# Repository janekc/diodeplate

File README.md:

# diodeplate
Plateshaped example PCB design for a portable partylamp

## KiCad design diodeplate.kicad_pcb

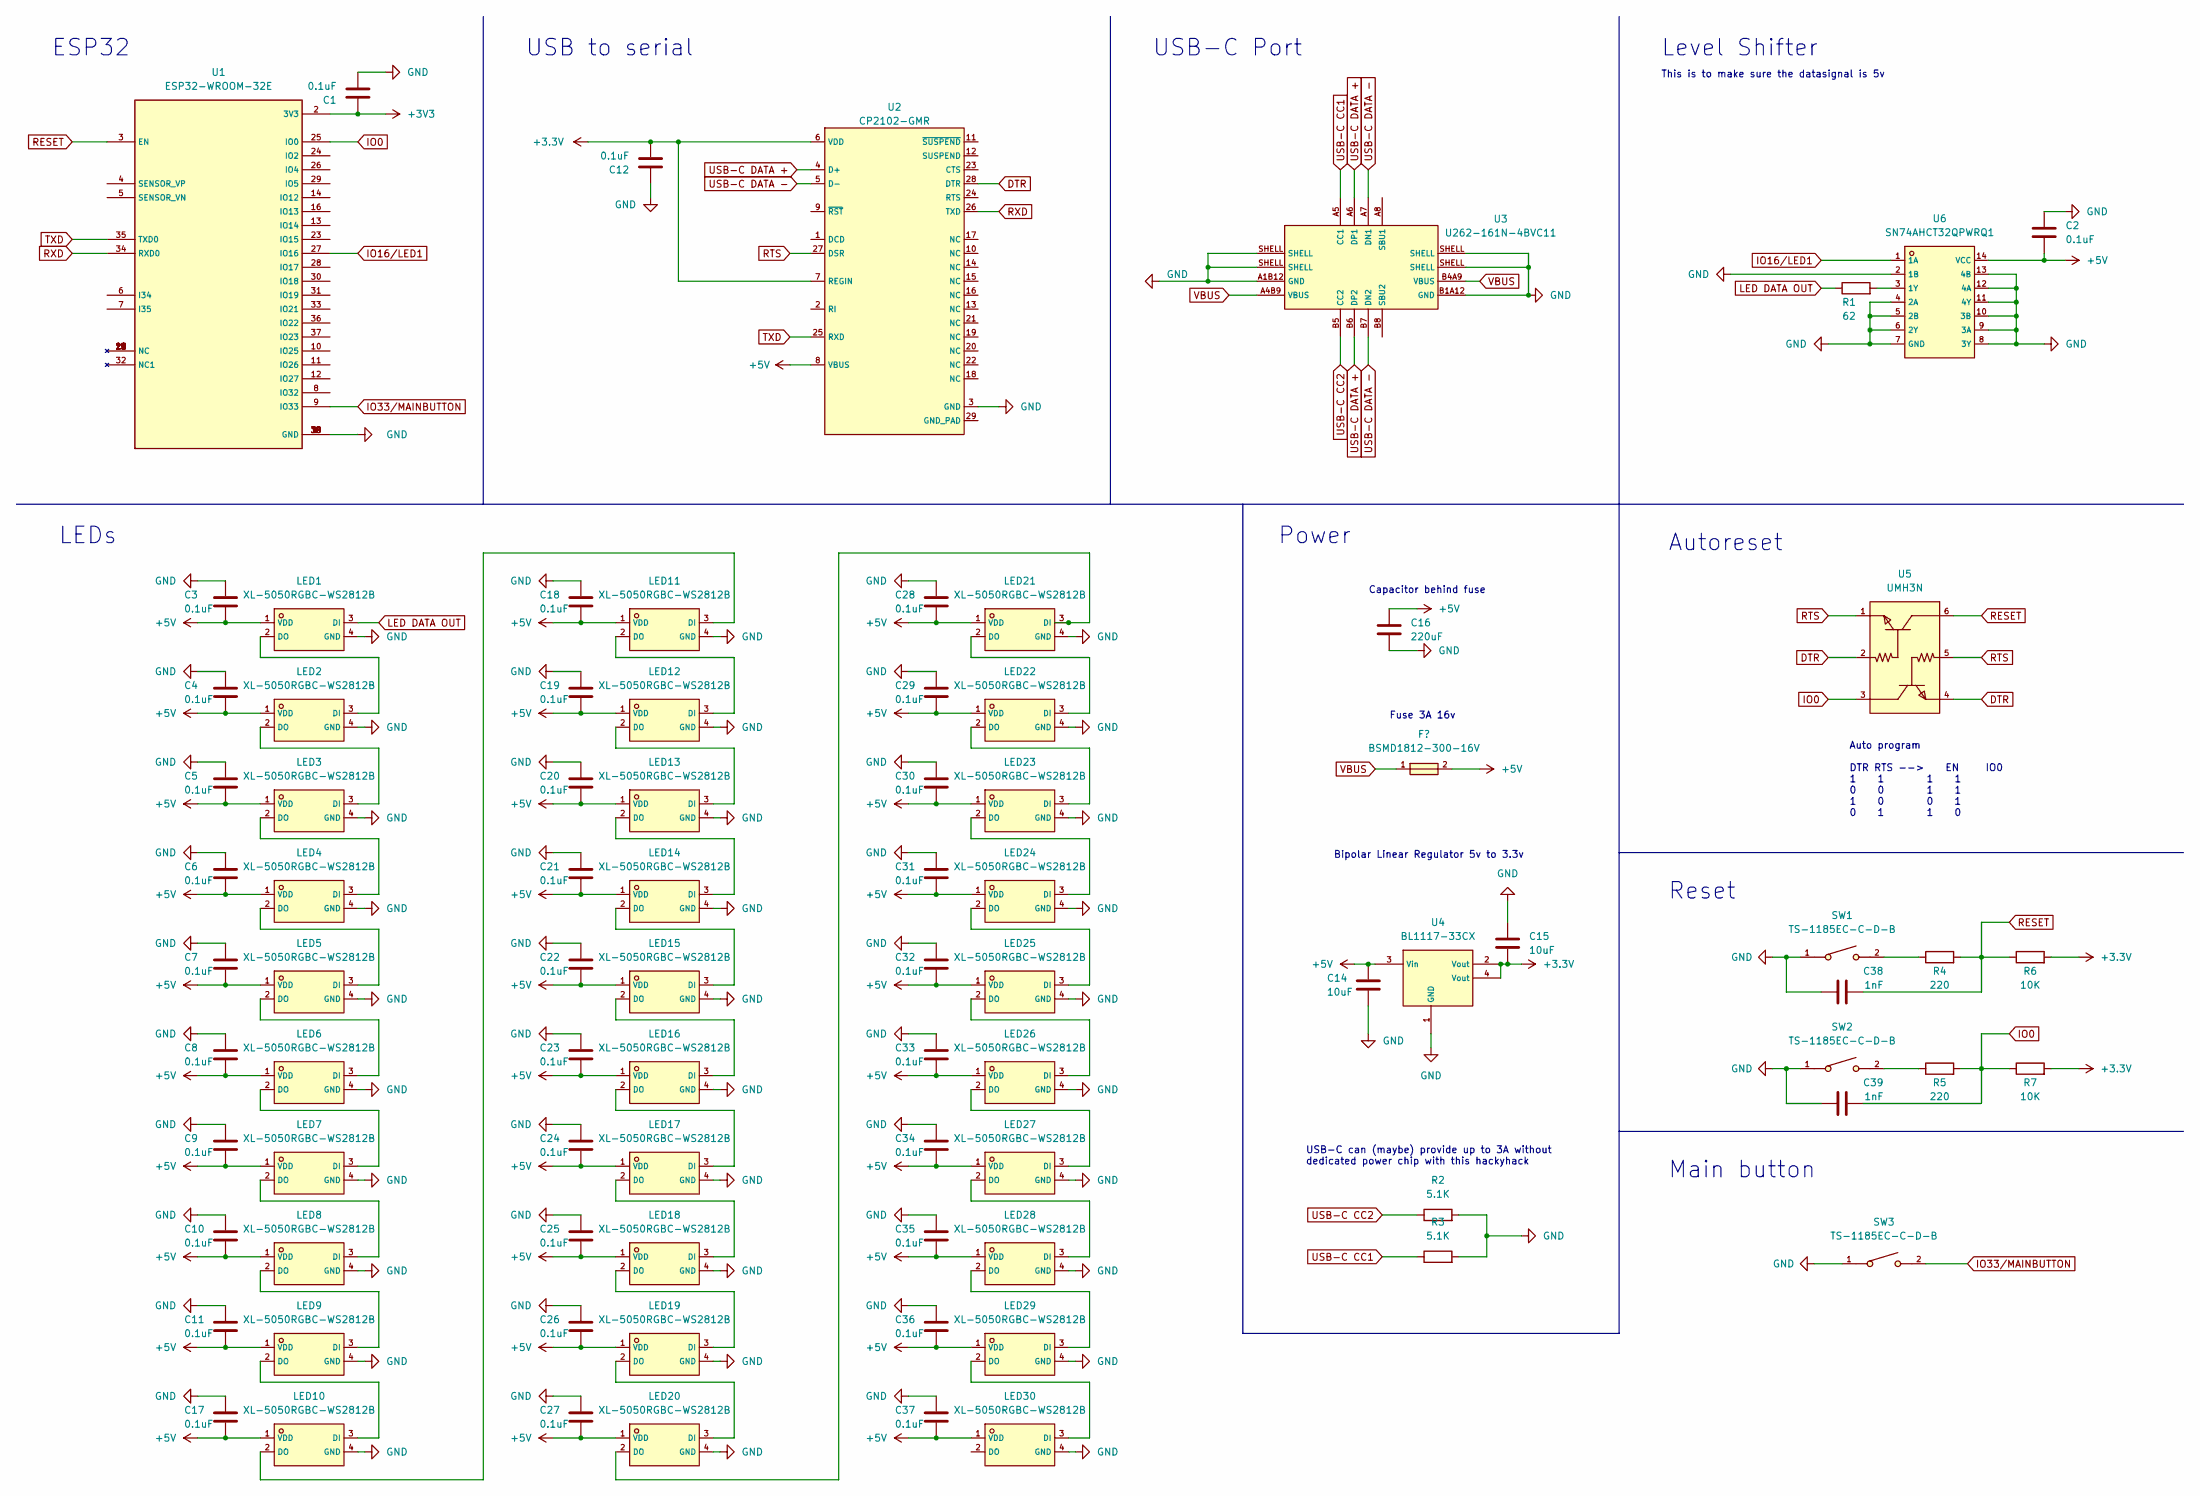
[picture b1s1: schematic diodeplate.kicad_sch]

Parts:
C1, C2, C3, C4, C5, C6, C7, C8, C9, C10, C11, C12, C17, C18, C19, C20, C21, C22, C23, C24, C25, C26, C27, C28, C29, C30, C31, C32, C33, C34, C35, C36, C37: 0.1uF; C_0603_1608Metric_Pad1.08x0.95mm_HandSolder
C14, C15: 10uF; C_0603_1608Metric_Pad1.08x0.95mm_HandSolder
C16: 220uF; C_Elec_6.3x5.4
C38, C39: 1nF; C_0603_1608Metric_Pad1.08x0.95mm_HandSolder; LCSC Part # C1588
LED1, LED2, LED3, LED4, LED5, LED6, LED7, LED8, LED9, LED10, LED11, LED12, LED13, LED14, LED15, LED16, LED17, LED18, LED19, LED20, LED21, LED22, LED23, LED24, LED25, LED26, LED27, LED28, LED29, LED30: XL-5050RGBC-WS2812B; LED_WS2812B_PLCC4_5.0x5.0mm_P3.2mm; LCSC # C2843785
R1: 62; R_0603_1608Metric_Pad0.98x0.95mm_HandSolder
R2, R3: 5.1K; R_0603_1608Metric_Pad0.98x0.95mm_HandSolder
R4, R5: 220; R_0603_1608Metric_Pad0.98x0.95mm_HandSolder; LCSC Part # C22962
R6, R7: 10K; R_0603_1608Metric_Pad0.98x0.95mm_HandSolder; LCSC Part # C25804
SW1, SW2, SW3: TS-1185EC-C-D-B; SW-SMD_4P-L3.7-W3.0-P1.50-LS4.7; LCSC # C318893
U1: ESP32-WROOM-32E; WIFI-SMD_ESP32-WROOM-32E; LCSC # C701341
U2: CP2102-GMR; QFN-28_L5.0-W5.0-P0.50-BL-EP; LCSC # C6568
U3: U262-161N-4BVC11; USB-3.1-SMD_U262-161N-4BVC11; LCSC # C319148
U4: BL1117-33CX; SOT-223-4_L6.5-W3.5-P2.30-LS7.0-BR; LCSC # C5400
U5: UMH3N; SC-70-6_L2.2-W1.3-P0.65-LS2.1-BR; LCSC # C62892
U6: SN74AHCT32QPWRQ1; TSSOP-14_L5.0-W4.4-P0.65-LS6.5-BL; LCSC # C507218

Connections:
+5V: C2.2, C3.2, C4.2, C5.2, C6.2, C7.2, C8.2, C9.2, C10.2, C11.2, C14.1, C16.1, C17.2, C18.2, C19.2, C20.2, C21.2, C22.2, C23.2, C24.2, C25.2, C26.2, C27.2, C28.2, C29.2, C30.2, C31.2, C32.2, C33.2, C34.2, C35.2, C36.2, C37.2, LED1.1 (VDD), LED2.1 (VDD), LED3.1 (VDD), LED4.1 (VDD), LED5.1 (VDD), LED6.1 (VDD), LED7.1 (VDD), LED8.1 (VDD), LED9.1 (VDD), LED10.1 (VDD), LED11.1 (VDD), LED12.1 (VDD), LED13.1 (VDD), LED14.1 (VDD), LED15.1 (VDD), LED16.1 (VDD), LED17.1 (VDD), LED18.1 (VDD), LED19.1 (VDD), LED20.1 (VDD), LED21.1 (VDD), LED22.1 (VDD), LED23.1 (VDD), LED24.1 (VDD), LED25.1 (VDD), LED26.1 (VDD), LED27.1 (VDD), LED28.1 (VDD), LED29.1 (VDD), LED30.1 (VDD), U2.8 (VBUS), U4.3 (Vin), U6.14 (VCC); also elsewhere on the board
DTR: U2.28 (DTR), U5.2 (B), U5.4 (E)
GND: C1.2, C2.1, C3.1, C4.1, C5.1, C6.1, C7.1, C8.1, C9.1, C10.1, C11.1, C12.1, C14.2, C15.1, C16.2, C17.1, C18.1, C19.1, C20.1, C21.1, C22.1, C23.1, C24.1, C25.1, C26.1, C27.1, C28.1, C29.1, C30.1, C31.1, C32.1, C33.1, C34.1, C35.1, C36.1, C37.1, C38.2, C39.2, LED1.4 (GND), LED2.4 (GND), LED3.4 (GND), LED4.4 (GND), LED5.4 (GND), LED6.4 (GND), LED7.4 (GND), LED8.4 (GND), LED9.4 (GND), LED10.4 (GND), LED11.4 (GND), LED12.4 (GND), LED13.4 (GND), LED14.4 (GND), LED15.4 (GND), LED16.4 (GND), LED17.4 (GND), LED18.4 (GND), LED19.4 (GND), LED20.4 (GND), LED21.4 (GND), LED22.4 (GND), LED23.4 (GND), LED24.4 (GND), LED25.4 (GND), LED26.4 (GND), LED27.4 (GND), LED28.4 (GND), LED29.4 (GND), LED30.4 (GND), R2.2, R3.2, SW1.1, SW2.1, SW3.1, U1.1 (GND), U1.15 (GND), U1.38 (GND), U1.39 (GND), U2.3 (GND), U3.A1B12 (GND), U3.B1A12 (GND), U3.SHELL, U4.1 (GND), U6.2 (1B), U6.4 (2A), U6.5 (2B), U6.6 (2Y), U6.7 (GND), U6.8 (3Y), U6.9 (3A), U6.10 (3B), U6.11 (4Y), U6.12 (4A), U6.13 (4B); also elsewhere on the board
IO0: C39.1, R5.2, R7.1, U1.25 (IO0), U5.3 (C)
IO16/LED1: U1.27 (IO16), U6.1 (1A)
IO33/MAINBUTTON: SW3.2, U1.9 (IO33); also elsewhere on the board
LED DATA OUT: LED1.3 (DI), R1.1
unnamed: LED1.2 (DO), LED2.3 (DI)
unnamed: LED2.2 (DO), LED3.3 (DI)
unnamed: LED3.2 (DO), LED4.3 (DI)
unnamed: LED4.2 (DO), LED5.3 (DI)
unnamed: LED5.2 (DO), LED6.3 (DI)
unnamed: LED6.2 (DO), LED7.3 (DI)
unnamed: LED7.2 (DO), LED8.3 (DI)
unnamed: LED8.2 (DO), LED9.3 (DI)
unnamed: LED10.2 (DO), LED11.3 (DI)
unnamed: LED9.2 (DO), LED10.3 (DI)
unnamed: LED11.2 (DO), LED12.3 (DI)
unnamed: LED12.2 (DO), LED13.3 (DI)
unnamed: LED13.2 (DO), LED14.3 (DI)
unnamed: LED14.2 (DO), LED15.3 (DI)
unnamed: LED15.2 (DO), LED16.3 (DI)
unnamed: LED16.2 (DO), LED17.3 (DI)
unnamed: LED17.2 (DO), LED18.3 (DI)
unnamed: LED18.2 (DO), LED19.3 (DI)
unnamed: LED19.2 (DO), LED20.3 (DI)
unnamed: LED20.2 (DO), LED21.3 (DI)
unnamed: LED21.2 (DO), LED22.3 (DI)
unnamed: LED22.2 (DO), LED23.3 (DI)
unnamed: LED23.2 (DO), LED24.3 (DI)
unnamed: LED24.2 (DO), LED25.3 (DI)
unnamed: LED25.2 (DO), LED26.3 (DI)
unnamed: LED26.2 (DO), LED27.3 (DI)
unnamed: LED27.2 (DO), LED28.3 (DI)
unnamed: LED28.2 (DO), LED29.3 (DI)
unnamed: LED29.2 (DO), LED30.3 (DI)
unnamed: R1.2, U6.3 (1Y)
unnamed 37: R4.1, SW1.2; also elsewhere on the board
unnamed 38: R5.1, SW2.2; also elsewhere on the board
RESET: C38.1, R4.2, R6.1, U1.3 (EN), U5.6 (C)
RTS: U2.27 (DSR), U5.1 (E), U5.5 (B)
RXD: U1.34 (RXD0), U2.26 (TXD)
TXD: U1.35 (TXD0), U2.25 (RXD)
USB-C CC1: R3.1, U3.A5 (CC1)
USB-C CC2: R2.1, U3.B5 (CC2)
USB-C DATA +: U2.4 (D+), U3.A6 (DP1), U3.B6 (DP2)
USB-C DATA -: U2.5 (D-), U3.A7 (DN1), U3.B7 (DN2)
VBUS: U3.A4B9 (VBUS), U3.B4A9 (VBUS); also elsewhere on the board

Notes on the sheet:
Autoreset
Capacitor behind fuse
USB to serial
USB-C Port
Power
USB-C can (maybe) provide up to 3A without dedicated power chip with this hackyhack
Main button
Bipolar Linear Regulator 5v to 3.3v
Fuse 3A 16v
This is to make sure the datasignal is 5v
Auto program DTR RTS --> EN IO0 1 1 1 1 0 0 1 1 1 0 0 1 0 1 1 0
Level Shifter
LEDs
Reset
ESP32

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
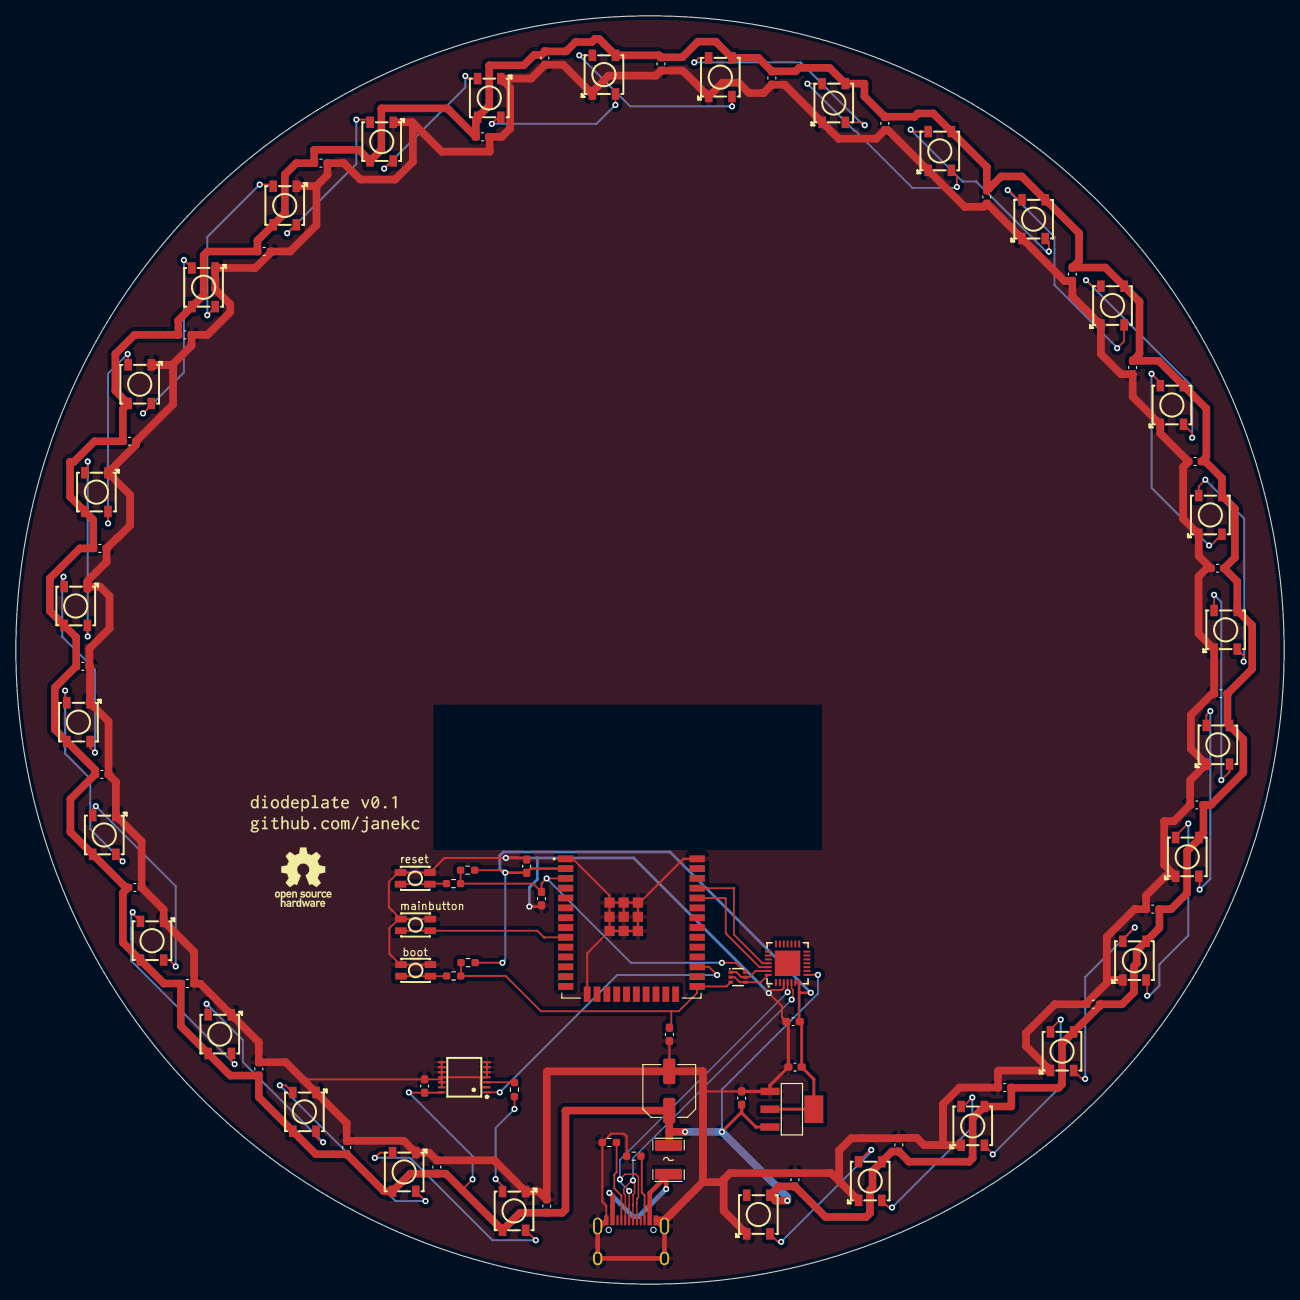
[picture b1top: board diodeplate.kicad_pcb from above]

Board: 2 copper layers, 164.0 x 164.0 mm, 85 parts (0 on the bottom side), 49 nets.

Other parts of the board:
F1: BSMD1812-300-16V; F1812
boot: TS-1185EC-C-D-B; SW-SMD_4P-L3.7-W3.0-P1.50-LS4.7
mainbutton: TS-1185EC-C-D-B; SW-SMD_4P-L3.7-W3.0-P1.50-LS4.7
reset: TS-1185EC-C-D-B; SW-SMD_4P-L3.7-W3.0-P1.50-LS4.7

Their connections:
+5V: F1.2; also elsewhere on the board
GND: boot.1, mainbutton.1, reset.1; also elsewhere on the board
IO33/MAINBUTTON: mainbutton.2; also elsewhere on the board
unnamed 37: reset.2; also elsewhere on the board
unnamed 38: boot.2; also elsewhere on the board
VBUS: F1.1; also elsewhere on the board

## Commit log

2022-05-06 add from example design
2022-05-07 add first pcb design
2022-05-07 leds arranged every 15cm
2022-05-11 finished traces, made plate bigger
2022-05-11 add jlcpscb folder
2022-05-15 added groundplate, update gitignore
2022-05-16 add open hardware logo and some text, resolved warnings
2022-05-16 remove dot on fuse footprint, exclude some errors
2022-05-18 pcb bestellt
2022-06-02 added stencil
2022-06-02 added rectangle for lasercutting stencil
2022-06-02 added stl file for 3d-printed case
2022-08-03 new case
2022-08-04 remove pcb from 3d model
